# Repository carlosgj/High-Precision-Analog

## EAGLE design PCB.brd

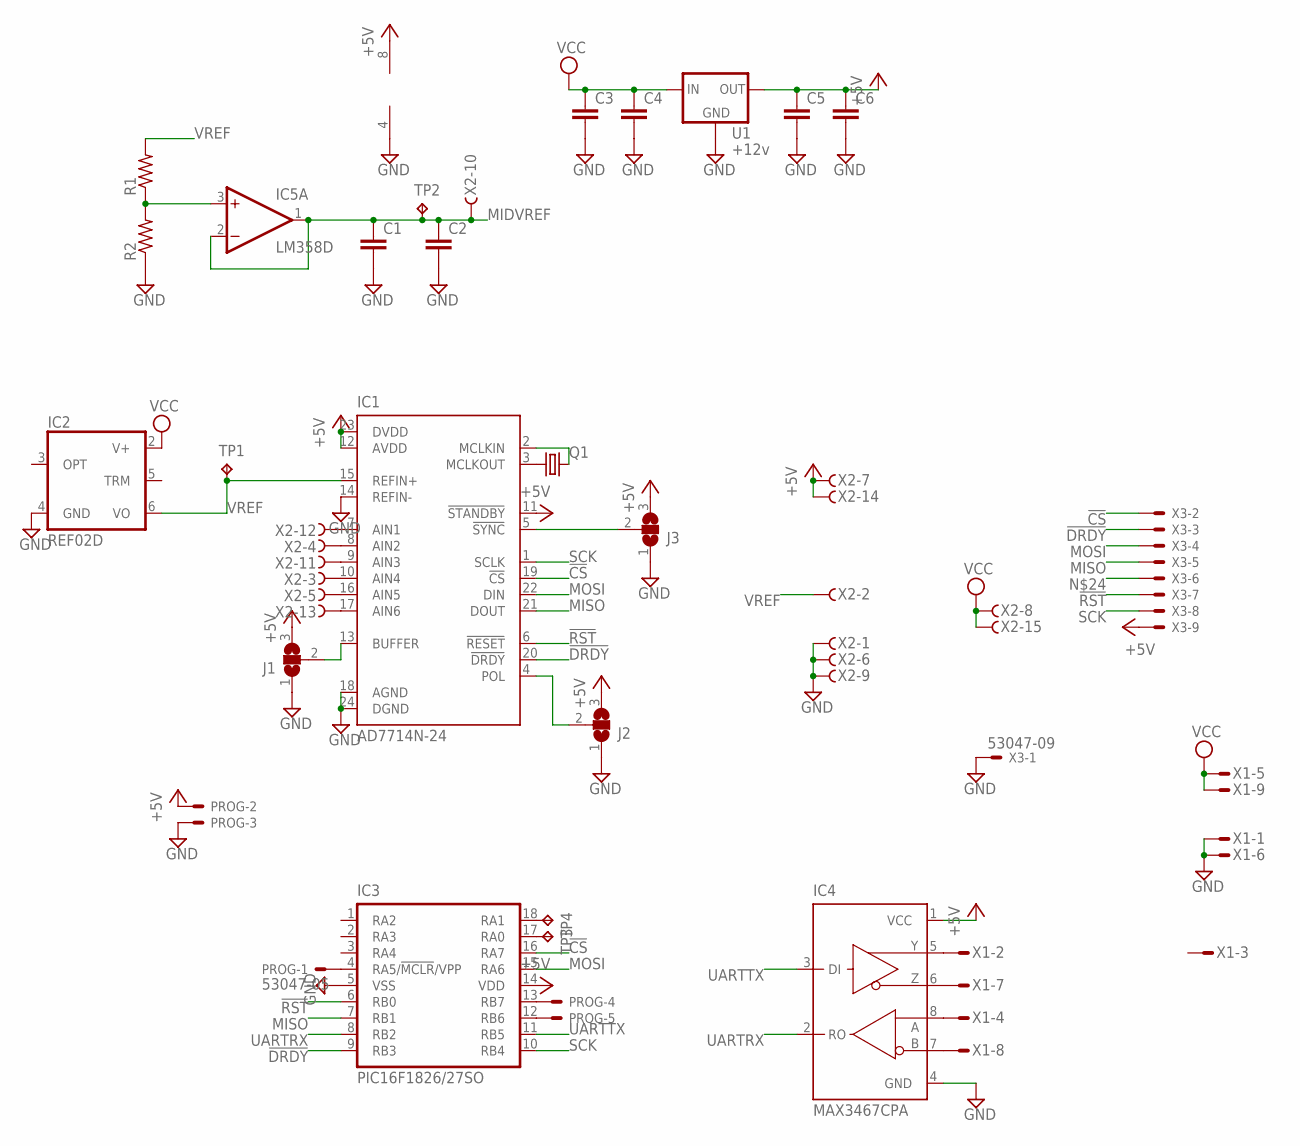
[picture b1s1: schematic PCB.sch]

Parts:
C1, C2, C3, C4, C5, C6: C-EUC1206K; C1206K
IC1: AD7714N-24; DIL24-3
IC2: REF02D; SO08
IC3: PIC16F1826/27SO; SO-18W
IC4: MAX3467CPA; SO08
IC5: LM358D; SO08
J1, J2, J3: SJ2W; SJ_2
PROG: 53047-05
Q1: CRYSTALHC49S; HC49/S
R1, R2: R-US_M1206; M1206
TP1, TP2, TP3, TP4: TPB1,27; B1,27
U1: +12v; TO-252
X1: M09HPS; M09HP
X2: F15HPS; F15HP
X3: 53047-09

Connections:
!CS: IC1.19 (!CS), IC3.16 (RA7), X3.2
!DRDY: IC1.20 (!DRDY), IC3.9 (RB3), X3.3
!RST: IC1.6 (!RESET), IC3.6 (RB0), X3.7
+5V: C5.1, C6.1, IC1.11 (!STANDBY), IC1.12 (AVDD), IC1.23 (DVDD), IC3.14 (VDD), IC4.1 (VCC), IC5.8 (V+), J1.3, J2.3, J3.3, PROG.2, U1.2 (OUT), X2.7, X2.14, X3.9
GND: C1.2, C2.2, C3.2, C4.2, C5.2, C6.2, IC1.14 (REFIN-), IC1.18 (AGND), IC1.24 (DGND), IC2.4 (GND), IC3.5 (VSS), IC4.4 (GND), IC5.4 (V-), J1.1, J2.1, J3.1, PROG.3, R2.1, U1.3 (GND), X1.1, X1.6, X2.1, X2.6, X2.9, X3.1
MIDVREF: C1.1, C2.1, IC5.1 (OUT), IC5.2 (-IN), TP2.TP, X2.10
MISO: IC1.21 (DOUT), IC3.7 (RB1), X3.5
MOSI: IC1.22 (DIN), IC3.15 (RA6), X3.4
unnamed: IC1.3 (MCLKOUT), Q1.1
unnamed: IC1.2 (MCLKIN), Q1.2
unnamed: IC1.13 (BUFFER), J1.2
unnamed: IC1.4 (POL), J2.2
unnamed: IC4.5 (Y), X1.2
unnamed: IC4.6 (Z), X1.7
unnamed: IC4.8 (A), X1.4
unnamed: IC4.7 (B), X1.8
unnamed: IC5.3 (+IN), R1.1, R2.2
unnamed: IC1.10 (AIN4), X2.3
unnamed: IC1.9 (AIN3), X2.11
unnamed: IC1.8 (AIN2), X2.4
unnamed: IC1.7 (AIN1), X2.12
unnamed: IC1.5 (!SYNC), J3.2
unnamed: IC1.16 (AIN5), X2.5
unnamed: IC1.17 (AIN6), X2.13
unnamed: IC3.4 (RA5/!MCLR!/VPP), PROG.1
unnamed: IC3.13 (RB7), PROG.4
unnamed: IC3.12 (RB6), PROG.5
unnamed: IC3.17 (RA0), TP3.TP
unnamed: IC3.18 (RA1), TP4.TP
SCK: IC1.1 (SCLK), IC3.10 (RB4), X3.8
UARTRX: IC3.8 (RB2), IC4.2 (RO)
UARTTX: IC3.11 (RB5), IC4.3 (DI)
VCC: C3.1, C4.1, IC2.2 (V+), U1.1 (IN), X1.5, X1.9, X2.8, X2.15
VREF: IC1.15 (REFIN+), IC2.6 (VO), R1.2, TP1.TP, X2.2

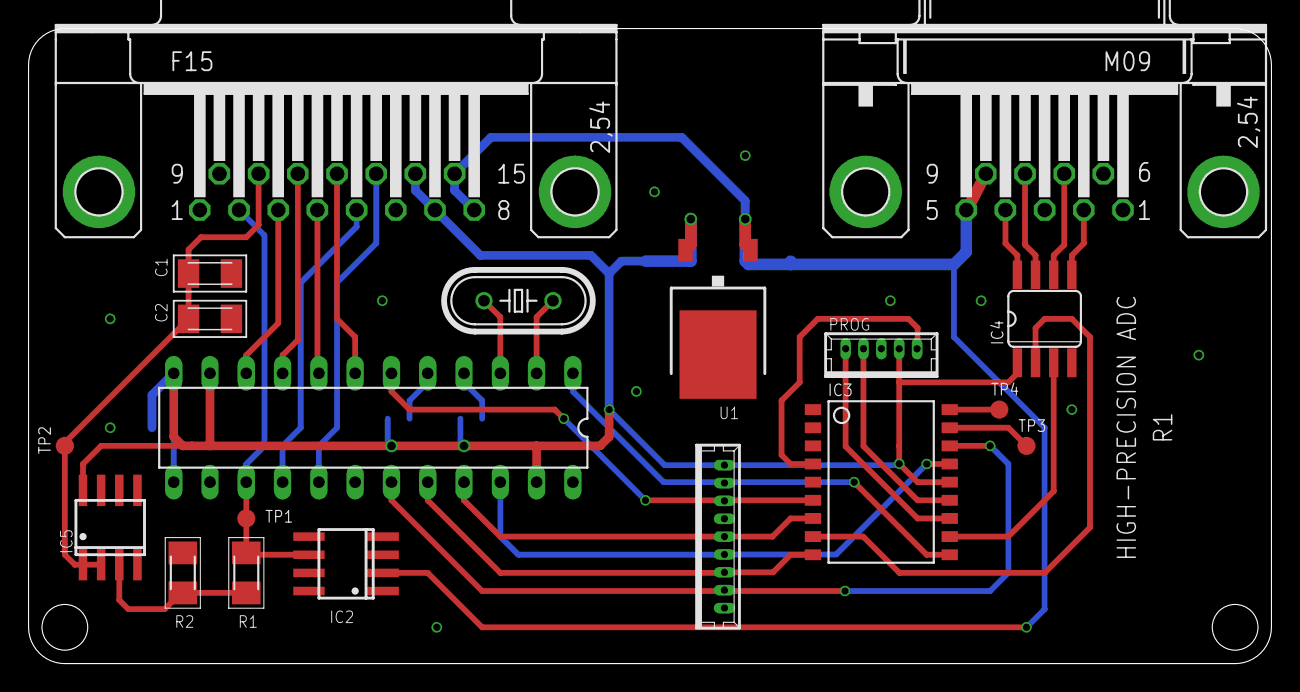
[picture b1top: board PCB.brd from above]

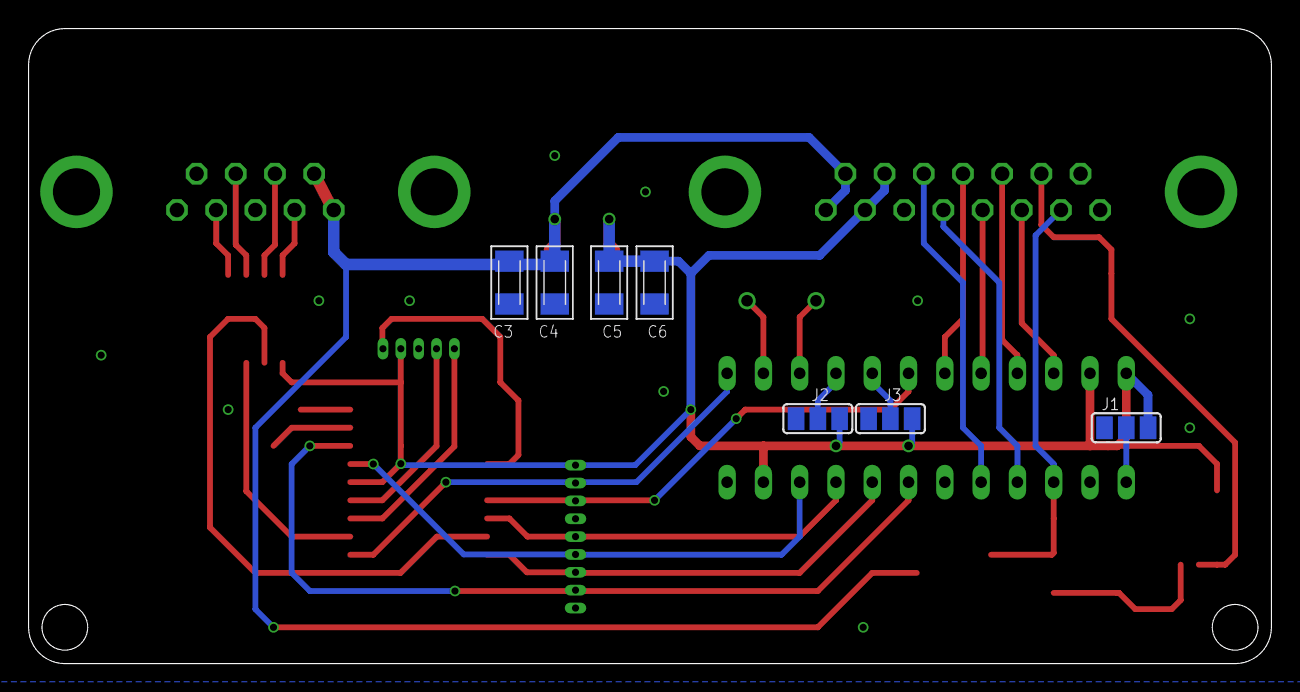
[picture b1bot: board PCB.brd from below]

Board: 2 copper layers, 87.0 x 44.5 mm, 26 parts (7 on the bottom side), 34 nets.

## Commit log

2021-03-06 HW r1

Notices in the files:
parts and their libraries:
SparkFun-IC-Power: Licensing: Creative Commons ShareAlike 4.0 International - https://creativecommons.org/licenses/by-sa/4.0
